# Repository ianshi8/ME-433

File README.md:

# ME-433
Repository for Northwestern's ME 433 Advanced Mechatronics Coursework (Spring Quarter, 2023)

This is an advanced class in mechatronic systems prototyping. In this course we learned how to design, solder, and debug a printed circuit board (PCB) and create physical prototypes with a laser cutter and 3d printer. We also learned advanced digital communication protocols like SPI and I2C, and advanced signal processing. 

The following repository contains the various assignments completed in this course.

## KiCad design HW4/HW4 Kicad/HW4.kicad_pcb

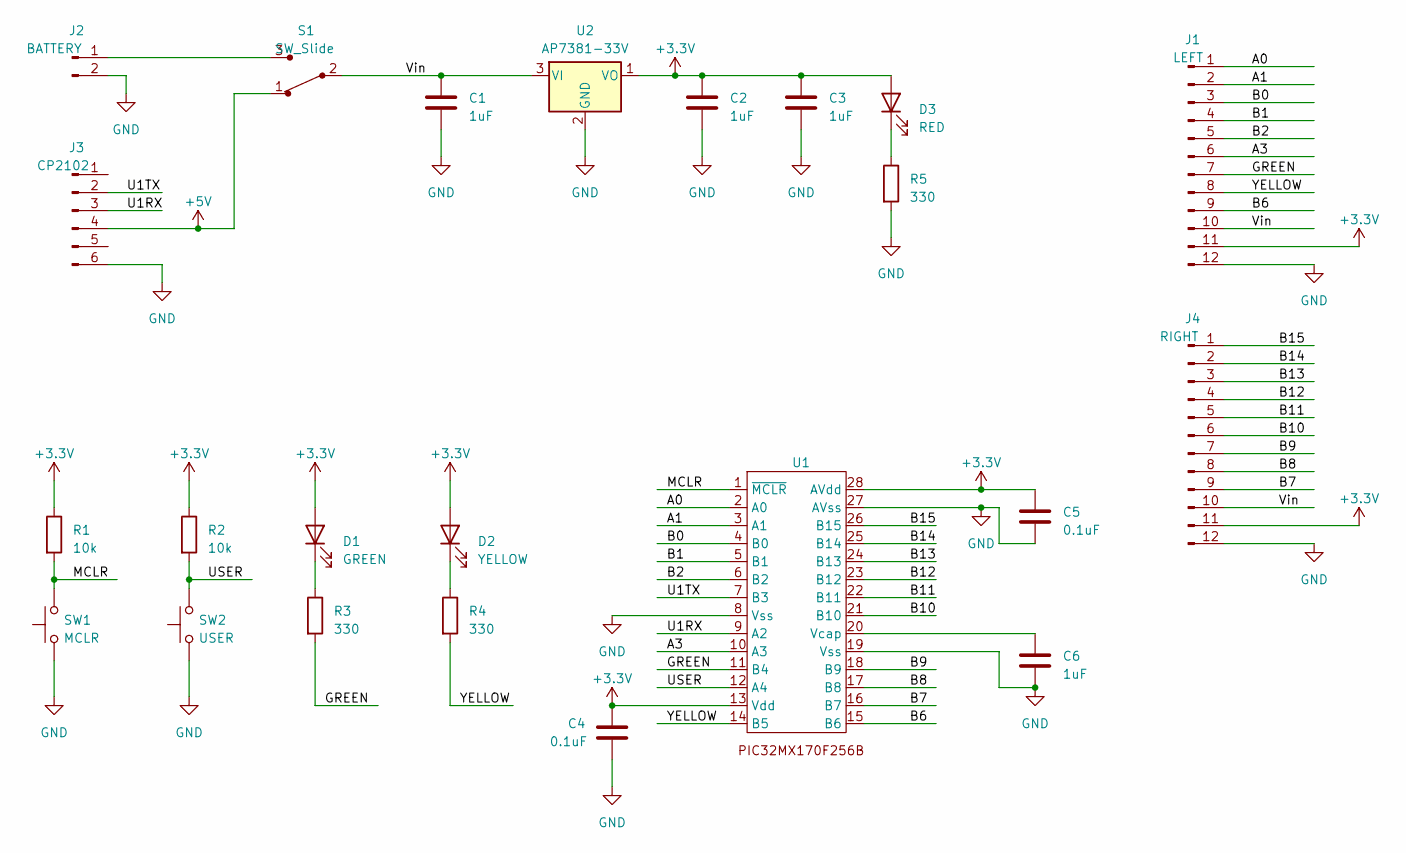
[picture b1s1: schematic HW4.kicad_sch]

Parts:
C1, C2, C3, C6: 1uF; C_Disc_D5.1mm_W3.2mm_P5.00mm
C4, C5: 0.1uF; C_Disc_D3.4mm_W2.1mm_P2.50mm
D1: GREEN; LED_D3.0mm
D2: YELLOW; LED_D3.0mm
D3: RED; LED_D3.0mm
J1: LEFT; PinSocket_1x12_P2.54mm_Vertical
J2: BATTERY; PinSocket_1x02_P2.54mm_Vertical
J3: CP2102; PinSocket_1x06_P2.54mm_Vertical
J4: RIGHT; PinSocket_1x12_P2.54mm_Vertical
R1, R2: 10k; R_Axial_DIN0207_L6.3mm_D2.5mm_P7.62mm_Horizontal
R3, R4, R5: 330; R_Axial_DIN0207_L6.3mm_D2.5mm_P7.62mm_Horizontal
S1: SW_Slide; SlideSW; MPN EG1218; Digi-Key_PN EG1903-ND
SW1: MCLR; PushButton
SW2: USER; PushButton
U1: DIP-28_W7.62mm_Socket
U2: AP7381-33V; TO-92L_Inline

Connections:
+3.3V: C2.1, C3.1, C4.1, C5.1, D1.2 (A), D2.2 (A), D3.2 (A), J1.11, J4.11, R1.1, R2.1, U1.13 (Vdd), U1.28 (AVdd), U2.1 (VO)
+5V: J3.4, S1.1
/A0: J1.1, U1.2 (A0)
/A1: J1.2, U1.3 (A1)
/A3: J1.6, U1.10 (A3)
/B0: J1.3, U1.4 (B0)
/B1: J1.4, U1.5 (B1)
/B2: J1.5, U1.6 (B2)
/B6: J1.9, U1.15 (B6)
/B7: J4.9, U1.16 (B7)
/B8: J4.8, U1.17 (B8)
/B9: J4.7, U1.18 (B9)
/B10: J4.6, U1.21 (B10)
/B11: J4.5, U1.22 (B11)
/B12: J4.4, U1.23 (B12)
/B13: J4.3, U1.24 (B13)
/B14: J4.2, U1.25 (B14)
/B15: J4.1, U1.26 (B15)
/GREEN: J1.7, R3.2, U1.11 (B4)
/MCLR: R1.2, SW1.2, U1.1 (~MCLR)
/U1RX: J3.3, U1.9 (A2)
/U1TX: J3.2, U1.7 (B3)
/USER: R2.2, SW2.2, U1.12 (A4)
/Vin: C1.1, J1.10, J4.10, S1.2, U2.3 (VI)
/YELLOW: J1.8, R4.2, U1.14 (B5)
GND: C1.2, C2.2, C3.2, C4.2, C5.2, C6.2, J1.12, J2.2, J3.6, J4.12, R5.2, SW1.1, SW2.1, U1.8 (Vss), U1.19 (Vss), U1.27 (AVss), U2.2 (GND)
unnamed: D1.1 (K), R3.1
unnamed: D2.1 (K), R4.1
unnamed: D3.1 (K), R5.1
unnamed: J2.1, S1.3
unnamed: C6.1, U1.20 (Vcap)

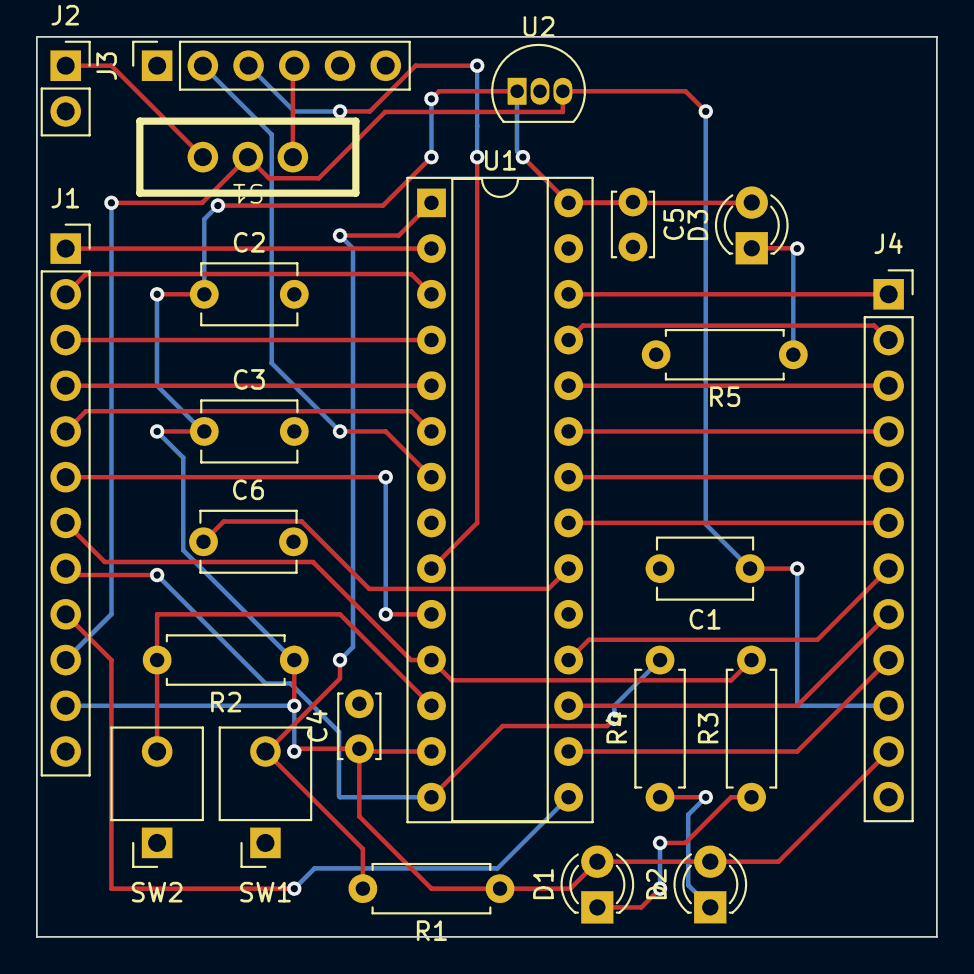
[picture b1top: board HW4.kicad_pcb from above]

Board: 2 copper layers, 50.0 x 50.0 mm, 23 parts (0 on the bottom side), 31 nets.

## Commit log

2023-03-30 Created HW2 Folder
2023-04-01 HW2 Code
2023-04-01 Recording
2023-04-04 HW3 Code + Recording
2023-04-07 HW4 Schematic
2023-04-07 HW4 Schematic Cleanup
2023-04-14 HW4 PCB Layout completed
2023-04-17 HW5 code and output
2023-04-19 Updated HW5 code
2023-04-19 HW6 code and demo
2023-04-21 HW 7 Code and plots
2023-04-26 Initialization for HW8
2023-04-26 HW 8 code and demo
2023-04-30 HW9a code and plots
2023-04-30 HW9 part b done before part a, renaming
2023-05-01 Added hw9a code and figures
2023-05-01 HW9 completed figures and code
2023-05-03 Mac updated and stuff changed?
2023-05-05 HW10 initial code
2023-05-08 Fixed hw10 code and added demo
2023-05-10 HW11 code and output
2023-05-20 HW 12 wheel cad png
2023-05-23 HW13 code and output
2023-05-23 updated hw12 wheel cad
2023-05-23 HW 12 box cad
2023-06-01 HW14 code and video
2023-06-02 HW14 Stuff
2023-06-05 HW15 Code and output
